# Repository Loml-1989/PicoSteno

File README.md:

# PicoSteno

A custom, 24-key stenotype keyboard powered by a raspberry pi pico. This board has direct pin wiring (meaning zero diodes) and Getron Strawberry Jelly switches (which are hot swappable) for an good stenography experience.

## Why?
I build this because I really wanted to try out steno keyboards but they are quite pricey so I couldn't buy em so I decided to make my very own full size steno keyboard.

## Gallery

## Features
- **Microcontroller:** Raspberry pi pico
- **Switches:** Getron Strawberry Jelly (Hot swappable)
- **Status Indicator:** WS2812B 2020 RGB LED
- **Firmware:** QMK (using the `geminipr` protocol)

## Firmware Flashing
1. Download the `picosteno.uf2` file
2. Hold the boot button on the pico
3. Connect it to computer
4. Move the `picosteno.uf2` file to the `RPI-RP2` disk which will appear
DONE!!! 

## Note
- Uses M2 screws
- CAD URL: https://cad.onshape.com/documents/52c8cac9818d188b0d83dccb/w/326c1203be3ba0b6302d81fb/e/90ae4f0d030c3e2e50035fcf

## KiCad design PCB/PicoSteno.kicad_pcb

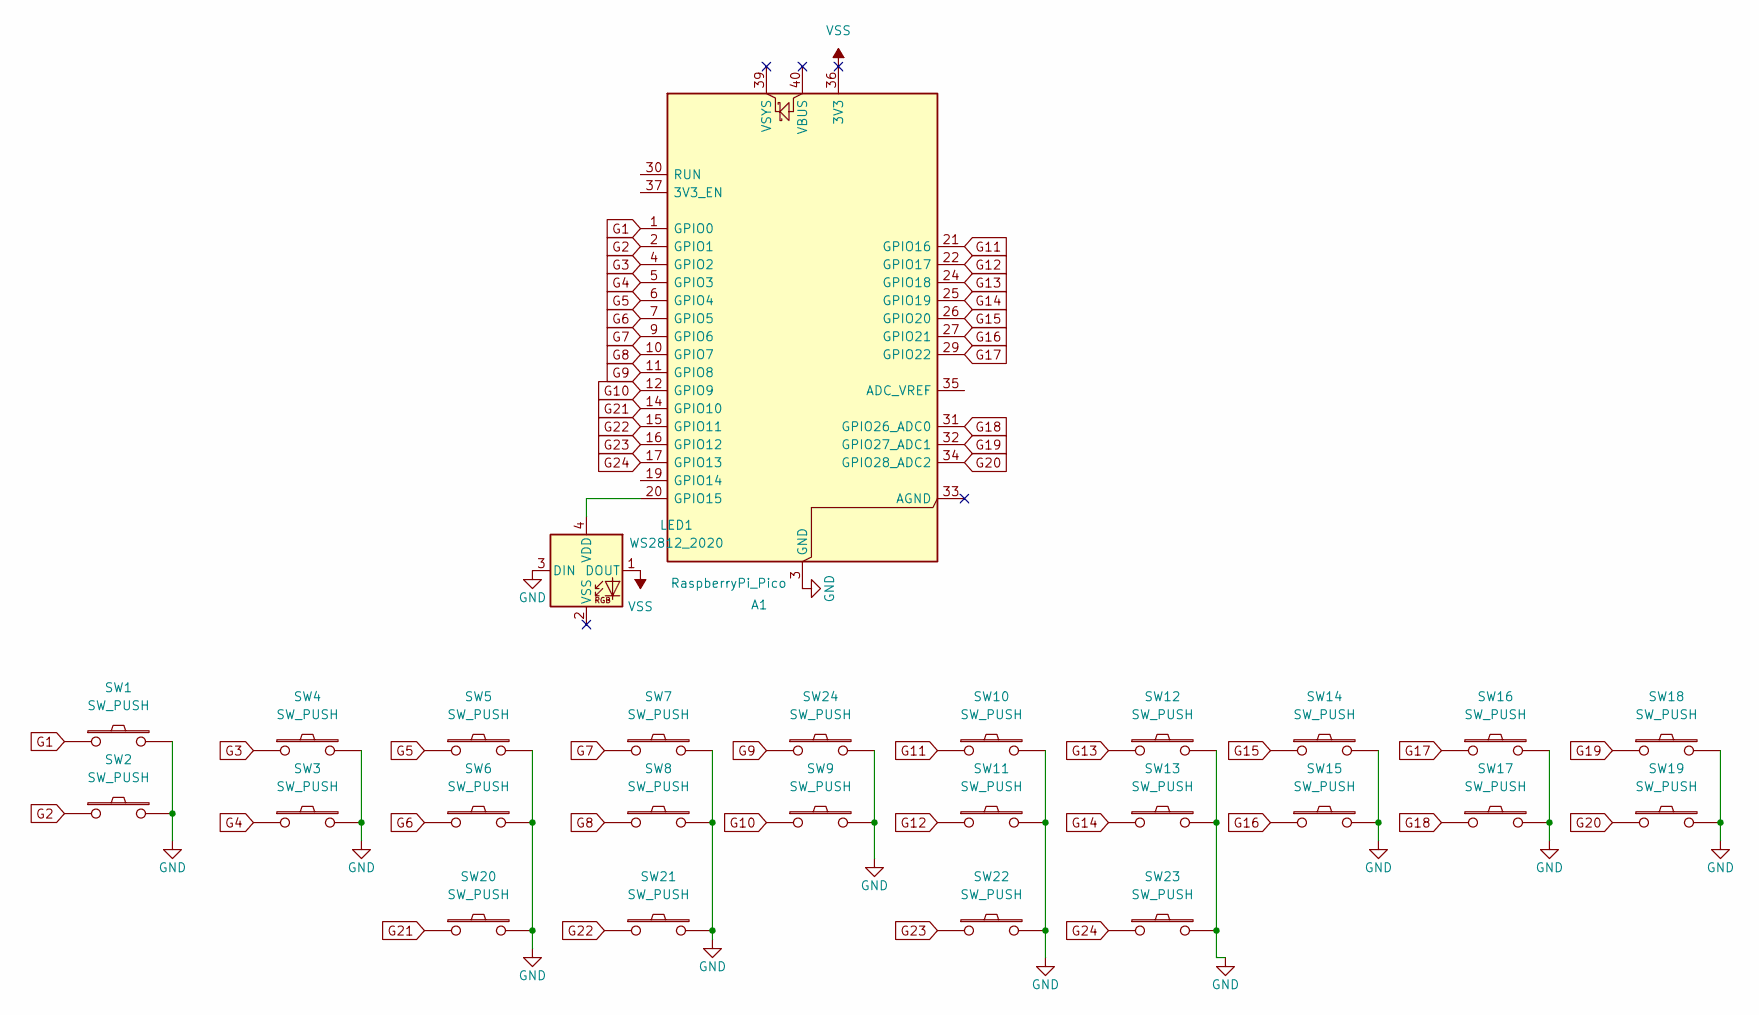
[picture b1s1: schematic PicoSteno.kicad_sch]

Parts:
A1: RaspberryPi_Pico; RaspberryPi_Pico_Common_Unspecified
LED1: WS2812_2020; LED_WS2812_2020
SW1, SW2, SW3, SW4, SW5, SW6, SW7, SW8, SW9, SW10, SW11, SW12, SW13, SW14, SW15, SW16, SW17, SW18, SW19, SW20, SW21, SW22, SW23, SW24: SW_PUSH; SW_Hotswap_Kailh_MX_1.00u

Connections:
G1: A1.1 (GPIO0), SW1.1
G2: A1.2 (GPIO1), SW2.1
G3: A1.4 (GPIO2), SW4.1
G4: A1.5 (GPIO3), SW3.1
G5: A1.6 (GPIO4), SW5.1
G6: A1.7 (GPIO5), SW6.1
G7: A1.9 (GPIO6), SW7.1
G8: A1.10 (GPIO7), SW8.1
G9: A1.11 (GPIO8), SW24.1
G10: A1.12 (GPIO9), SW9.1
G11: A1.21 (GPIO16), SW10.1
G12: A1.22 (GPIO17), SW11.1
G13: A1.24 (GPIO18), SW12.1
G14: A1.25 (GPIO19), SW13.1
G15: A1.26 (GPIO20), SW14.1
G16: A1.27 (GPIO21), SW15.1
G17: A1.29 (GPIO22), SW16.1
G18: A1.31 (GPIO26_ADC0), SW17.1
G19: A1.32 (GPIO27_ADC1), SW18.1
G20: A1.34 (GPIO28_ADC2), SW19.1
G21: A1.14 (GPIO10), SW20.1
G22: A1.15 (GPIO11), SW21.1
G23: A1.16 (GPIO12), SW22.1
G24: A1.17 (GPIO13), SW23.1
GND: A1.3 (GND), A1.8 (GND), A1.13 (GND), A1.18 (GND), A1.23 (GND), A1.28 (GND), A1.38 (GND), LED1.3 (DIN), SW1.2, SW2.2, SW3.2, SW4.2, SW5.2, SW6.2, SW7.2, SW8.2, SW9.2, SW10.2, SW11.2, SW12.2, SW13.2, SW14.2, SW15.2, SW16.2, SW17.2, SW18.2, SW19.2, SW20.2, SW21.2, SW22.2, SW23.2, SW24.2
unnamed: A1.20 (GPIO15), LED1.4 (VDD)
VSS: A1.36 (3V3), LED1.1 (DOUT)

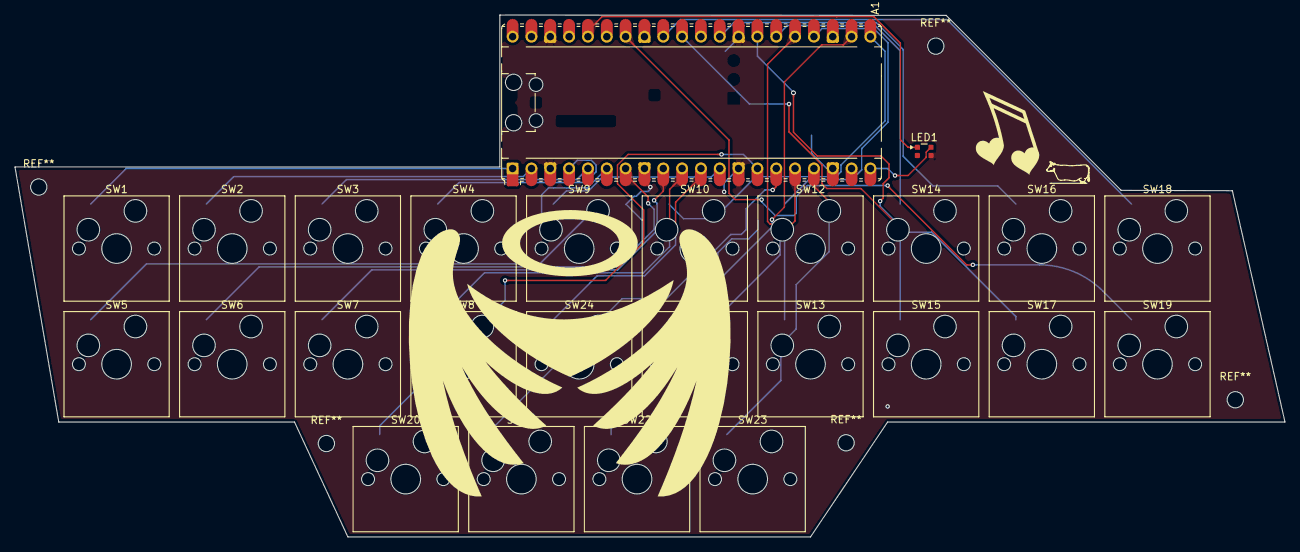
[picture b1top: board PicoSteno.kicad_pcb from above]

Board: 2 copper layers, 171.3 x 70.4 mm, 26 parts (0 on the bottom side), 27 nets.

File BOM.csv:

Designator,Footprint,Quantity,Value,Link,Price (USD)
A1,RaspberryPi_Pico_Common_Unspecified,1,RaspberryPi_Pico,https://robu.in/product/raspberry-pi-pico/,$4.03
D1,WS2812B_2020_4Pin,1,WS2812B_2020,https://robu.in/product/sme-ws2812b-2020-addressable-rgb-pix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,$0.10
"SW1, SW10, SW11, SW12, SW13, SW14, SW15, SW16, SW17, SW18, SW19, SW2, SW20, SW21, SW22, SW23, SW24, SW3, SW4, SW5, SW6, SW7, SW8, SW9",SW_Hotswap_Kailh_MX,30(24 used),SW_PUSH,https://neomacro.in/products/jerrzi-mx-hotswap-sockets?varia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,$2.00
Gateron Strawberry Jelly Switch,,30(24 used),,https://neomacro.in/products/gateron-strawberry-jelly-switch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,$5.00
PCB,,5,,https://www.lioncircuits.com/pcb-fabrication,$23.00
Keycaps,,30(24 used),,https://neomacro.in/products/dsa-blank-keycaps?variant=51613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,$5.00
Total,,,,,$39.13
